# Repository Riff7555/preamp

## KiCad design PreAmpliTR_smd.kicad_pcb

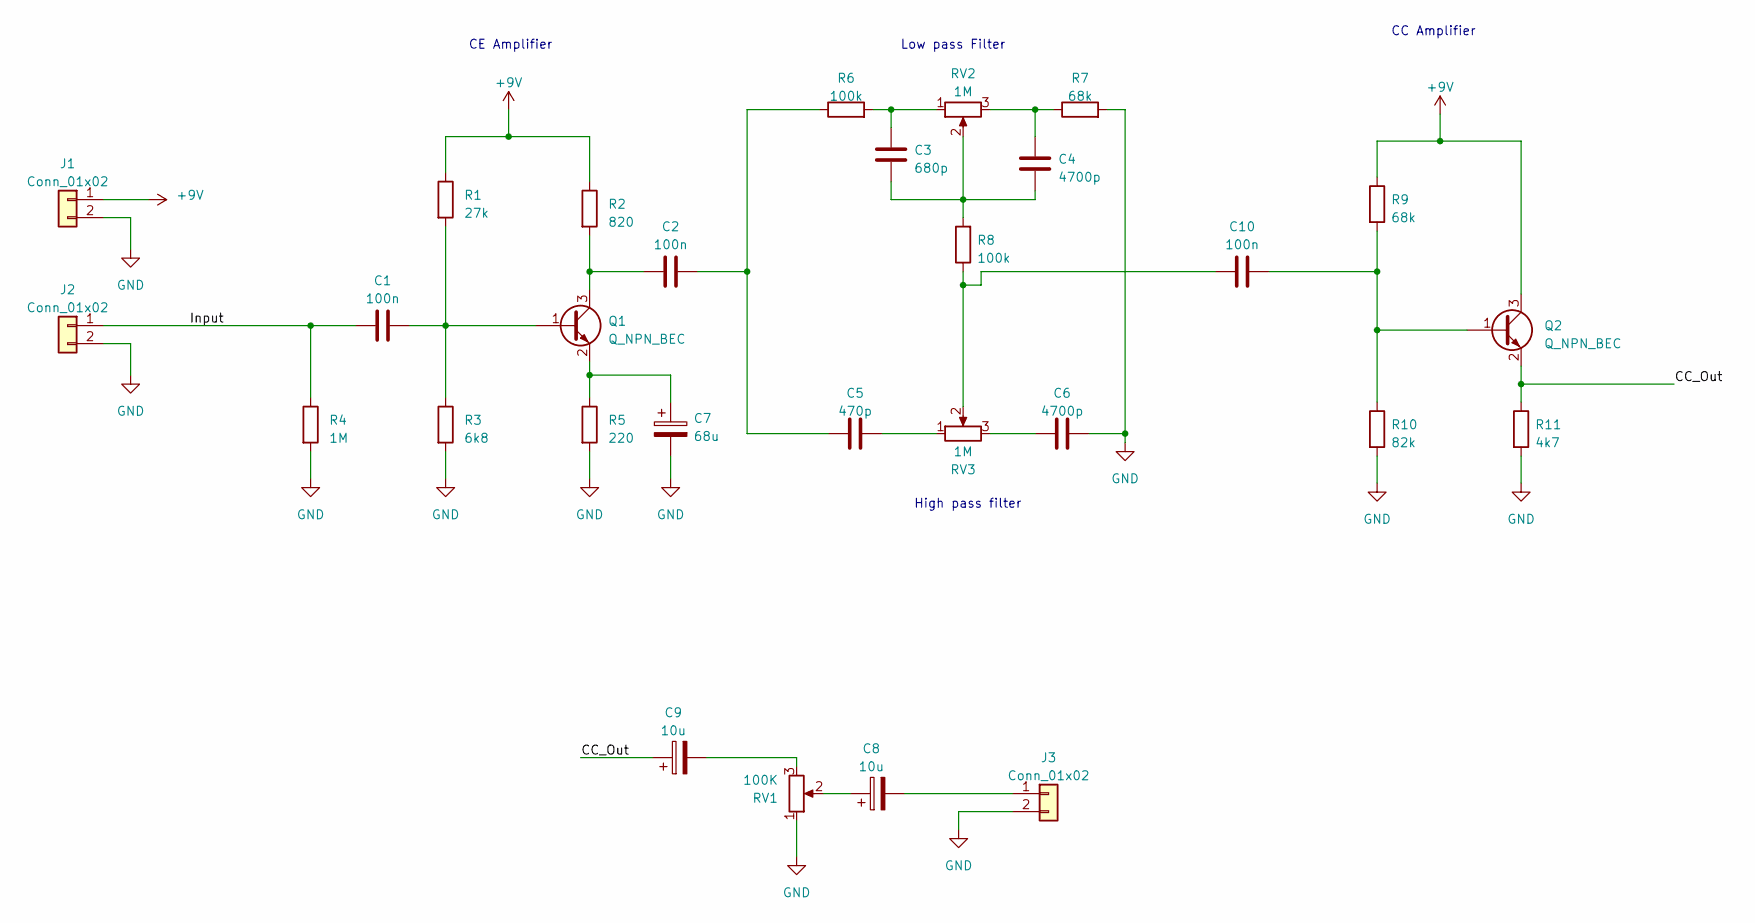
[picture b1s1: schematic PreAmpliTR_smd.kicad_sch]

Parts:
C1, C2, C10: 100n; C_0805_2012Metric_Pad1.18x1.45mm_HandSolder
C3: 680p; C_0805_2012Metric_Pad1.18x1.45mm_HandSolder
C4, C6: 4700p; C_0805_2012Metric_Pad1.18x1.45mm_HandSolder
C5: 470p; C_0805_2012Metric_Pad1.18x1.45mm_HandSolder
C7: 68u; C_0805_2012Metric_Pad1.18x1.45mm_HandSolder
C8, C9: 10u; C_0805_2012Metric_Pad1.18x1.45mm_HandSolder
J1, J2, J3: Conn_01x02; TerminalBlock_bornier-2_P5.08mm
Q1, Q2: Q_NPN_BEC; TSOT-23
R1: 27k; R_0805_2012Metric_Pad1.20x1.40mm_HandSolder
R2: 820; R_0805_2012Metric_Pad1.20x1.40mm_HandSolder
R3: 6k8; R_0805_2012Metric_Pad1.20x1.40mm_HandSolder
R4: 1M; R_0805_2012Metric_Pad1.20x1.40mm_HandSolder
R5: 220; R_0805_2012Metric_Pad1.20x1.40mm_HandSolder
R6, R8: 100k; R_0805_2012Metric_Pad1.20x1.40mm_HandSolder
R7, R9: 68k; R_0805_2012Metric_Pad1.20x1.40mm_HandSolder
R10: 82k; R_0805_2012Metric_Pad1.20x1.40mm_HandSolder
R11: 4k7; R_0805_2012Metric_Pad1.20x1.40mm_HandSolder
RV1: 100K; Potentiometer_Piher_PC-16_Single_Vertical
RV2, RV3: 1M; Potentiometer_Piher_PC-16_Single_Vertical

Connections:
+9V: J1.1, Q2.3 (C), R1.1, R2.1, R9.1
/CC_Out: C9.1, Q2.2 (E), R11.1; also elsewhere on the board
/Input: C1.1, J2.1, R4.1
GND: C6.1, C7.2, J1.2, J2.2, J3.2, R3.2, R4.2, R5.2, R7.2, R10.2, R11.2, RV1.1
unnamed: C2.2, C5.2, R6.1
unnamed: C3.1, C4.1, R8.2, RV2.2
unnamed: C3.2, R6.2, RV2.1
unnamed: C4.2, R7.1, RV2.3
unnamed: C5.1, RV3.1
unnamed: C6.2, RV3.3
unnamed: C8.1, RV1.2
unnamed: C9.2, RV1.3
unnamed: C10.1, R8.1, RV3.2
unnamed: C8.2, J3.1
unnamed: C1.2, Q1.1 (B), R1.2, R3.1
unnamed: C2.1, Q1.3 (C), R2.2
unnamed: C7.1, Q1.2 (E), R5.1
unnamed 17: C10.2, Q2.1 (B), R9.2, R10.1; also elsewhere on the board

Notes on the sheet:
CC Amplifier
CE Amplifier
Low pass Filter
High pass filter

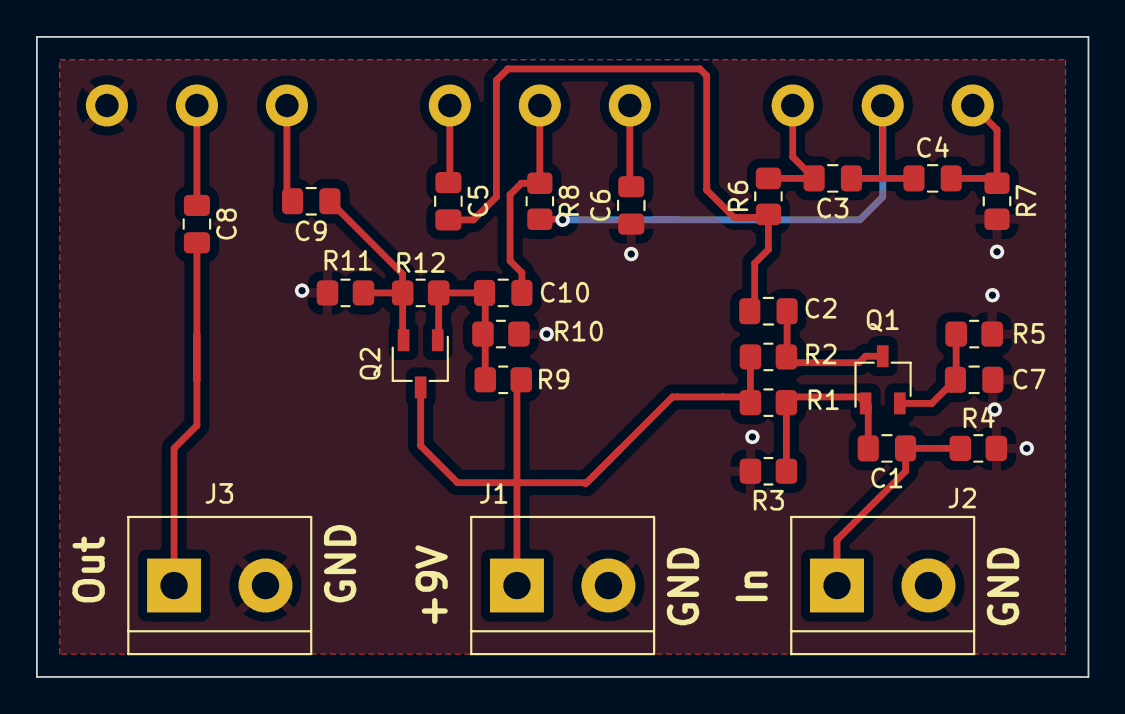
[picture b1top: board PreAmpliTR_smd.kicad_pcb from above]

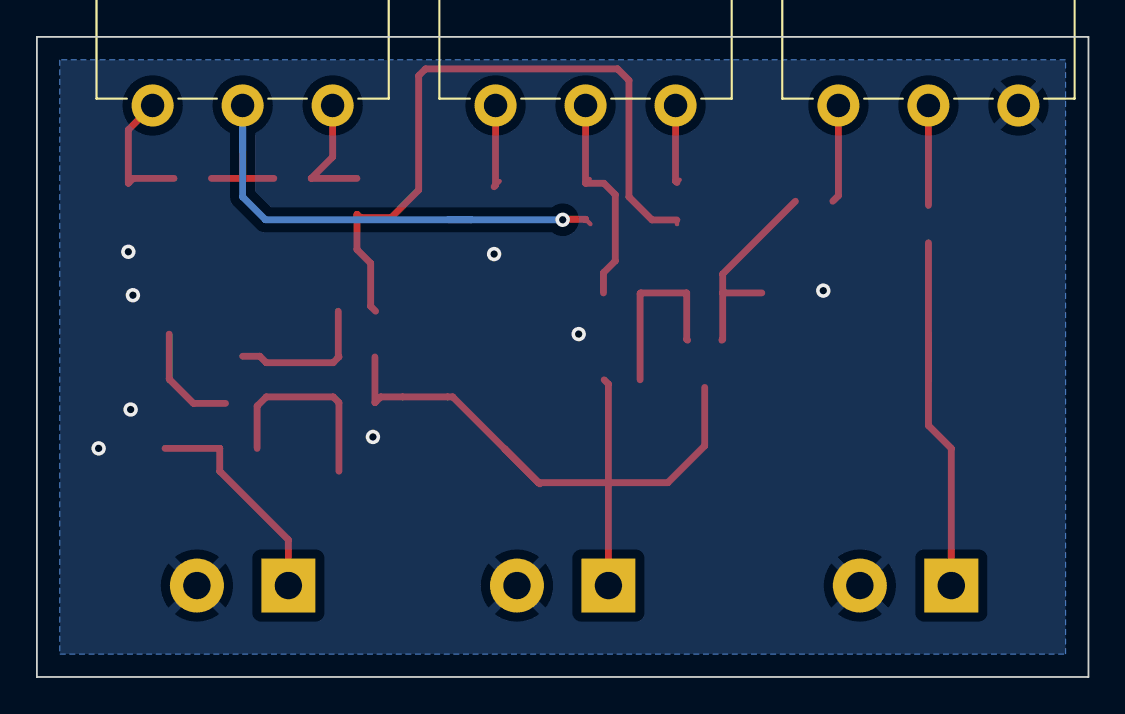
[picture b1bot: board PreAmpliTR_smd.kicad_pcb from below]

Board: 2 copper layers, 58.4 x 35.6 mm, 30 parts (3 on the bottom side), 18 nets.

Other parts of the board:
R12: 0; R_0805_2012Metric_Pad1.20x1.40mm_HandSolder

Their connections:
/CC_Out: R12.2; also elsewhere on the board
unnamed 17: R12.1; also elsewhere on the board

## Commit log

2024-03-13 cambio de valores de los filtros
2024-03-19 cambio de bloques: ec - filtro - cc - salida
